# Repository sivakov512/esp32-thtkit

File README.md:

# ESP32 THT Development Kits
**Ultra-Compact Through-Hole Development Boards for ESP32**

This repository contains design files and documentation for ultra-compact, through-hole (THT) friendly development boards based on Espressif ESP32 microcontrollers. These boards are designed for easy integration into breadboard and other through-hole prototyping environments.

## Available Development Kits

| DevKit | Description | SoC | Features |
|--------|-------------|-----|----------|
| [ESP32-C3-THTKIT](esp32-c3-thtkit/) | Ultra-compact ESP32-C3 development board with THT headers | ESP32-C3FH4 | WiFi, Bluetooth 5 (LE), RISC-V single-core |
| [ESP32-H2-THTKIT](esp32-h2-thtkit/) | Ultra-compact ESP32-H2 development board with THT headers | ESP32-H2FH4 | 802.15.4 (Thread, Zigbee), Bluetooth 5 (LE), RISC-V single-core |

## Key Features

- **Ultra-compact form factor**: Minimal dimensions for tight integration
- **Breadboard friendly**: Design optimized for breadboard prototyping
- **THT headers**: Standard 2.54mm pitch through-hole pins
- **Smart header layout**: Bottom header deliberately offset by 1.27mm (half pitch) to prevent accidental shorts in breadboards
- **Simple power supply**: 3.3V to 12V input with onboard LDO
- **Essential pins exposed**: Focused on providing the most important functionality
- **UART debug access**: Dedicated UART pins for easy programming and debugging
- **KiCad design files**: Complete open-source hardware design

## Design Philosophy

These development kits are designed with several principles in mind:
- **Minimal but complete**: Only essential components while maintaining full functionality
- **Direct integration**: Design that works in final projects, not just for prototyping
- **Hackable**: Easy to modify and adapt to specific needs
- **Open design**: Full schematics and PCB files available

## Getting Started

Visit each development kit's directory for specific documentation:

- [ESP32-C3-THTKIT Documentation](esp32-c3-thtkit/)
- [ESP32-H2-THTKIT Documentation](esp32-h2-thtkit/)

## License

This project is released under the [MIT License](LICENSE).

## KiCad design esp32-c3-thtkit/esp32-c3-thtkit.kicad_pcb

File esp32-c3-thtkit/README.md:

# ESP32-C3-THTKIT
**Ultra-Compact THT-Friendly DevKit**

---

## Overview

ESP32-C3-THTKIT is an ultra-compact development board based on the ESP32-C3FH4 SoC. Designed for direct THT integration, it exposes only essential functionality in a minimal form factor. UART pins are easily accessible at the top for in-circuit development.

---

## Pinout

- Left header (THT): VIN, GPIO2 to GPIO19
- Right header (THT): GND, GPIO17 to GPIO12 (FSPI2 by default)
- Bottom header (THT): GPIO4 to GPIO7 (JTAG by default)
- Top edge: UART TX/RX pins
- BOOT/RESET: pad-based activation (short to GND)
- Pin pitch: 2.54 mm standard
- Bottom header deliberately offset by 1.27 mm (half pitch) to prevent accidental shorts when inserted into a breadboard

---

## Programming & Debugging

- UART programming recommended via top pins
- JTAG available on bottom header (default mapping)
- No USB functionality

---

## Electrical

- Input Voltage: 3.3V to 12V
- On-board LDO stabilizes to 3.3V
- No onboard USB

---

## Mechanical

- Dimensions: 24.47 mm x 17.88 mm
- 3x THT headers: left, right, and optional bottom (user-soldered)

---

## Datasheet

[📄 ESP32-H2-THTKIT Datasheet (PDF)](docs/Datasheet.pdf)

[📄 ESP32-H2 Datasheet (Espressif)](https://cdn.jsdelivr.net/gh/sivakov512/kicad-library@master/datasheets/MCU/Espressif/Espressif_ESP32-H2.pdf)

---

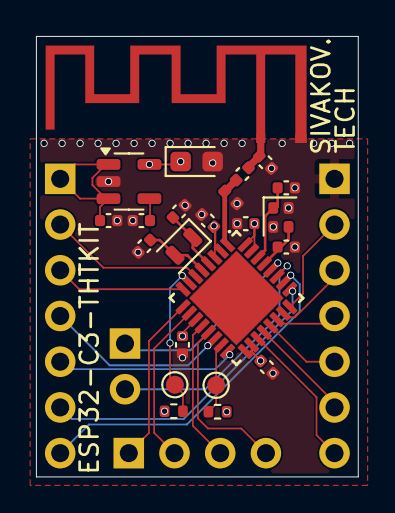
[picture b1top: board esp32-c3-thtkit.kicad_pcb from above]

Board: 4 copper layers, 17.9 x 24.5 mm, 27 parts (0 on the bottom side), 30 nets.

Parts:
AE1: Antenna_Chip; Antenna_PCB_Espressif_2.4GHz_Left
C1: 1m 6.3V X7R; C_0402_1005Metric
C2: 470p 6.3V X7R; C_0402_1005Metric
C3: 2.2m 6.3V TANT; CP_EIA-2012-12_Kemet-R
C4, C5, C6, C8: 100n 6.3V X7R; C_0402_1005Metric
C7: 5.6p C0G; C_0402_1005Metric
C9: 2.2p C0G; C_0402_1005Metric
C10, C13: 15p 6.3V C0G; C_0402_1005Metric
C11, C12: 25p 6.3V C0G; C_0402_1005Metric
J1: PIN_GROUP_1; PinHeader_1x07_P2.54mm_Vertical_NoSilk
J2: PIN_GROUP_3; PinHeader_1x07_P2.54mm_Vertical_NoSilk
J3: PIN_GROUP_2; PinHeader_1x04_P2.54mm_Vertical_NoSilk
J4: UART; PinHeader_1x02_P2.54mm_Vertical_NoSilk
L1: 3.9 nH; L_0402_1005Metric
R1, R2: 10k; R_0402_1005Metric
TP1, TP2: TestPoint; TestPoint_Pad_D1.0mm
U1: MIC5219-3.3YM5; SOT-23-5
U2: ESP32-C3; VFQFN_32_1EP_5x5mm_P0.5mm_EP3.2x3.2mm_Compact
Y1: 32.768kHz ±20ppm CL12.5pF; Crystal_SMD_2012-2Pin_2.0x1.2mm
Y2: 40MHz ±10ppm CL8pF; Crystal_SMD_1612-4Pin_1.6x1.2mm

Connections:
+3.3V: C3.1, C4.2, C5.2, C6.2, C8.2, R1.2, R2.2, U1.5 (OUT), U2.2 (VDD3P3), U2.3 (VDD3P3), U2.11 (VDD3P3_RTC), U2.17 (VDD3P3_CPU), U2.18 (VDD_SPI), U2.31 (VDDA), U2.32 (VDDA)
/BOOT: R1.1, TP1.1, U2.15 (GPIO9)
/GPIO2: J2.2, U2.6 (GPIO2)
/GPIO3: J2.3, U2.8 (GPIO3)
/GPIO8: J2.4, U2.14 (GPIO8)
/GPIO10: J2.5, U2.16 (GPIO10)
/GPIO18: J2.6, U2.25 (GPIO18)
/GPIO19: J2.7, U2.26 (GPIO19)
/MTCK: J3.3, U2.12 (MTCK)
/MTDI: J3.2, U2.10 (MTDI)
/MTDO: J3.4, U2.13 (MTDO)
/MTMS: J3.1, U2.9 (MTMS)
/RESET: R2.1, TP2.1, U2.7 (CHIP_EN)
/RF: C7.2, L1.1, U2.1 (LNA_IN)
/SPICLK: J1.4, U2.22 (SPICLK)
/SPICS0: J1.5, U2.21 (SPICS0)
/SPID: J1.3, U2.23 (SPID)
/SPIHD: J1.7, U2.19 (SPIHD)
/SPIQ: J1.2, U2.24 (SPIQ)
/SPIWP: J1.6, U2.20 (SPIWP)
/U0RXD: J4.2, U2.27 (U0RXD)
/U0TXD: J4.1, U2.28 (U0TXD)
/XTAL_32K_N: C12.2, U2.5 (XTAL_32K_N), Y1.2
/XTAL_32K_P: C11.2, U2.4 (XTAL_32K_P), Y1.1
/XTAL_N: C13.2, U2.29 (XTAL_N), Y2.3
/XTAL_P: C10.1, U2.30 (XTAL_P), Y2.1
GND: AE1.2 (PCB_Trace), C1.1, C2.1, C3.2, C4.1, C5.1, C6.1, C8.1, C9.1, C10.2, C11.1, C12.1, C13.1, J1.1, L1.2, U1.2 (GND), U2.33 (GND), Y2.2, Y2.4
unnamed: AE1.1 (FEED), C7.1, C9.2
unnamed: C2.2, U1.4 (BP)
VIN: C1.2, J2.1, U1.1 (IN), U1.3 (EN)

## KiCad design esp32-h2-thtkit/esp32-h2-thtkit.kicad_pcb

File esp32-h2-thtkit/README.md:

# ESP32-H2-THTKIT
**Ultra-Compact THT-Friendly DevKit**

---

## Overview

ESP32-H2-THTKIT is an ultra-compact development board based on the ESP32-H2FH4 SoC. Designed for direct integration into through-hole (THT) projects, it contains only the essential components and remains breadboard-friendly. UART debug pins are routed to the top for easy access during development, regardless of installation density.

---

## Pinout

- Left header (THT): GPIO0 to GPIO5 (also FSPI2-capable)
- Right header (THT): VIN, GND, GPIO27 to GPIO22
- Bottom header (THT): GPIO8, GPIO10, GPIO11, GPIO12 (can be used as JTAG)
- Top edge: UART TX/RX pins
- BOOT/RESET: pad-based activation (short to GND)
- Pin pitch: 2.54 mm standard
- Bottom header deliberately offset by 1.27 mm (half pitch) to prevent accidental shorts when inserted into a breadboard

---

## Programming & Debugging

- UART programming recommended via top pins
- JTAG support via GPIO8/10/11/12 (if remapped)
- No USB functionality

---

## Electrical

- Input Voltage: 3.3V to 12V
- On-board LDO stabilizes to 3.3V
- No onboard USB

---

## Mechanical

- Dimensions: 21.8 mm x 17.88 mm
- 3x THT headers: left, right, and optional bottom (user-soldered)

---

## Datasheet

[📄 ESP32-C3-THTKIT Datasheet (PDF)](docs/Datasheet.pdf)

[📄 ESP32-C3 Datasheet (Espressif)](https://cdn.jsdelivr.net/gh/sivakov512/kicad-library@master/datasheets/MCU/Espressif/Espressif_ESP32-C3.pdf)

---

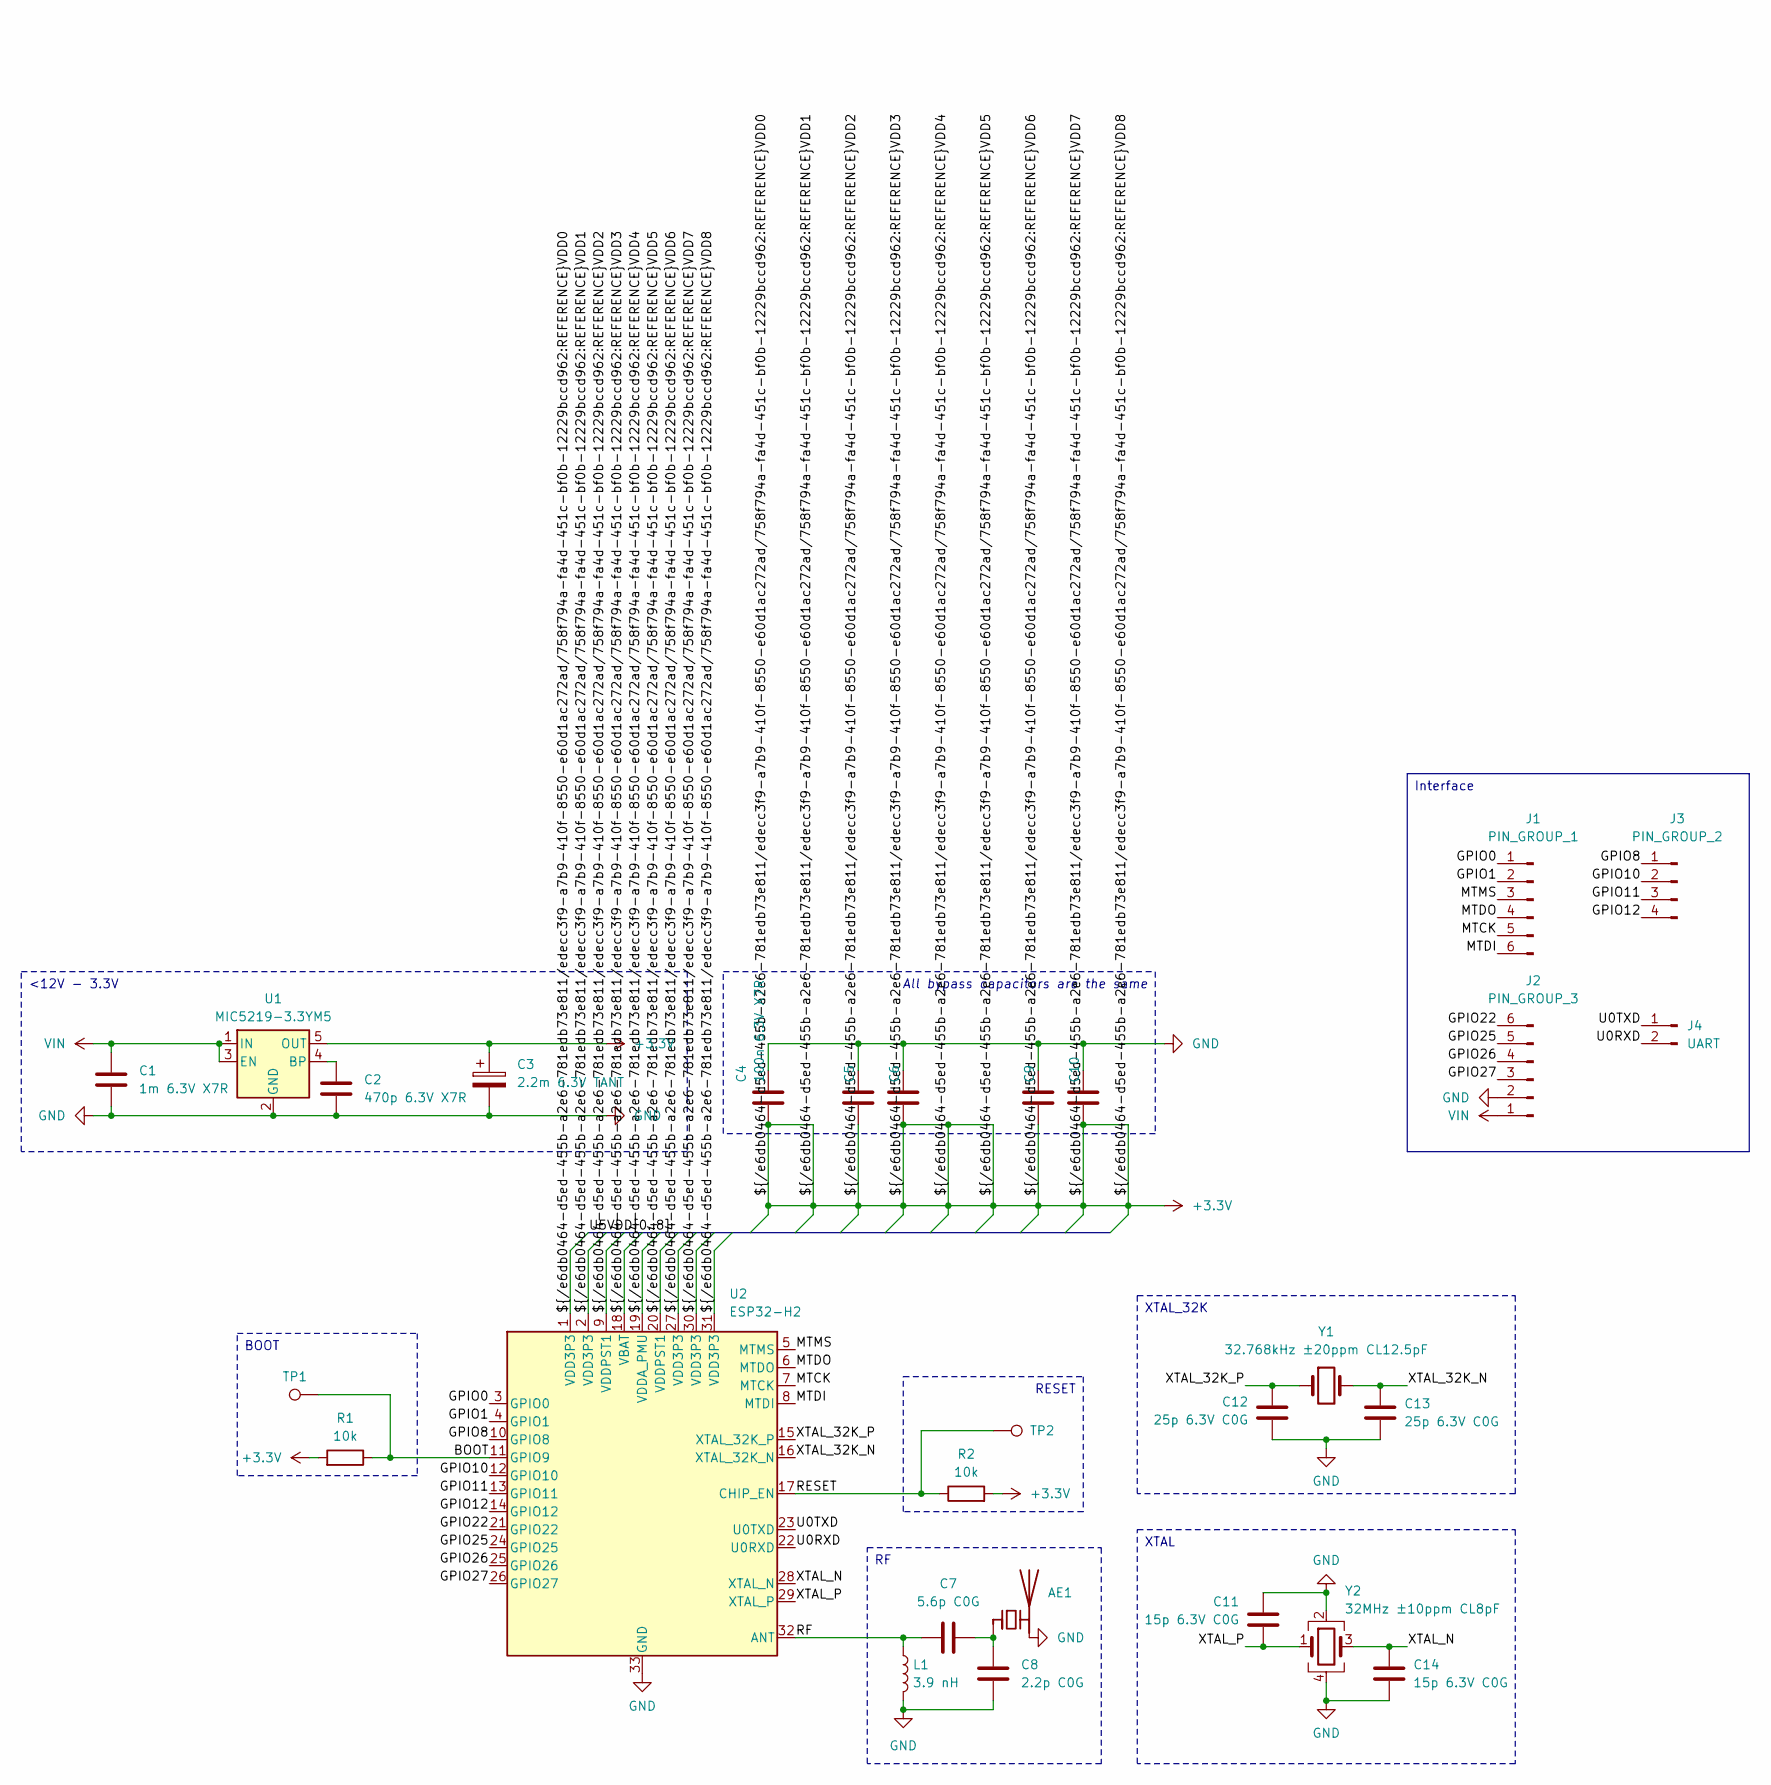
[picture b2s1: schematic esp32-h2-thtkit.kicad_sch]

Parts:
AE1: Antenna_Chip; Antenna_PCB_Espressif_2.4GHz_Right
C1: 1m 6.3V X7R; C_0402_1005Metric; LCSC PN C307427
C2: 470p 6.3V X7R; C_0402_1005Metric; LCSC PN C1537
C3: 2.2m 6.3V TANT; CP_EIA-2012-12_Kemet-R; LCSC PN C444770
C4, C5, C6, C9, C10: 100n 6.3V X7R; C_0402_1005Metric; LCSC PN C309458
C7: 5.6p C0G; C_0402_1005Metric; LCSC PN C1574
C8: 2.2p C0G; C_0402_1005Metric; LCSC PN C1559
C11, C14: 15p 6.3V C0G; C_0402_1005Metric; LCSC PN C1548
C12, C13: 25p 6.3V C0G; C_0402_1005Metric; LCSC PN C1556
J1: PIN_GROUP_1; PinHeader_1x06_P2.54mm_Vertical_NoSilk
J2: PIN_GROUP_3; PinHeader_1x06_P2.54mm_Vertical_NoSilk
J3: PIN_GROUP_2; PinHeader_1x04_P2.54mm_Vertical_NoSilk
J4: UART; PinHeader_1x02_P2.54mm_Vertical_NoSilk; LCSC PN C7501580
L1: 3.9 nH; L_0402_1005Metric; LCSC PN C77109
R1, R2: 10k; R_0402_1005Metric; LCSC PN C25744
TP1, TP2: TestPoint; TestPoint_Pad_D1.0mm
U1: MIC5219-3.3YM5; SOT-23-5; LCSC PN C29613
U2: ESP32-H2; TQFN_32_1EP_4x4mm_P0.4mm_EP2.4x2.4mm_Compact; LCSC PN C22470214
Y1: 32.768kHz ±20ppm CL12.5pF; Crystal_SMD_2012-2Pin_2.0x1.2mm; LCSC PN C55208
Y2: 32MHz ±10ppm CL8pF; Crystal_SMD_1612-4Pin_1.6x1.2mm; LCSC PN C7301921

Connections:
+3.3V: C3.1, C4.2, C5.2, C6.2, C9.2, C10.2, R1.2, R2.2, U1.5 (OUT), U2.1 (VDD3P3), U2.2 (VDD3P3), U2.9 (VDDPST1), U2.18 (VBAT), U2.19 (VDDA_PMU), U2.20 (VDDPST1), U2.27 (VDD3P3), U2.30 (VDD3P3), U2.31 (VDD3P3)
/BOOT: R1.1, TP1.1, U2.11 (GPIO9)
/GPIO0: J1.1, U2.3 (GPIO0)
/GPIO1: J1.2, U2.4 (GPIO1)
/GPIO8: J3.1, U2.10 (GPIO8)
/GPIO10: J3.2, U2.12 (GPIO10)
/GPIO11: J3.3, U2.13 (GPIO11)
/GPIO12: J3.4, U2.14 (GPIO12)
/GPIO22: J2.6, U2.21 (GPIO22)
/GPIO25: J2.5, U2.24 (GPIO25)
/GPIO26: J2.4, U2.25 (GPIO26)
/GPIO27: J2.3, U2.26 (GPIO27)
/MTCK: J1.5, U2.7 (MTCK)
/MTDI: J1.6, U2.8 (MTDI)
/MTDO: J1.4, U2.6 (MTDO)
/MTMS: J1.3, U2.5 (MTMS)
/RESET: R2.1, TP2.1, U2.17 (CHIP_EN)
/RF: C7.2, L1.1, U2.32 (ANT)
/U0RXD: J4.2, U2.22 (U0RXD)
/U0TXD: J4.1, U2.23 (U0TXD)
/XTAL_32K_N: C13.2, U2.16 (XTAL_32K_N), Y1.2
/XTAL_32K_P: C12.2, U2.15 (XTAL_32K_P), Y1.1
/XTAL_N: C14.2, U2.28 (XTAL_N), Y2.3
/XTAL_P: C11.1, U2.29 (XTAL_P), Y2.1
GND: AE1.2 (PCB_Trace), C1.1, C2.1, C3.2, C4.1, C5.1, C6.1, C8.1, C9.1, C10.1, C11.2, C12.1, C13.1, C14.1, J2.2, L1.2, U1.2 (GND), U2.33 (GND), Y2.2, Y2.4
unnamed: AE1.1 (FEED), C7.1, C8.2
unnamed: C2.2, U1.4 (BP)
VIN: C1.2, J2.1, U1.1 (IN), U1.3 (EN)

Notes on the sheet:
XTAL
RESET
XTAL_32K
All bypass capacitors are the same
BOOT
Interface
<12V - 3.3V

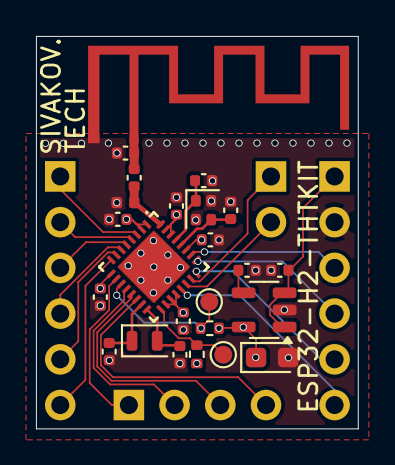
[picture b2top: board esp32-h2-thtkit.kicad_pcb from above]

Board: 4 copper layers, 17.9 x 21.8 mm, 28 parts (0 on the bottom side), 28 nets.

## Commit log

2025-05-28 Ignore KiCad specific stuff
2025-05-28 Define esp32-h2 schematic
2025-05-28 Use connectors without silkscreen to place them right on the corner
2025-05-28 Basic components layout
2025-05-29 Full schematic and PCB layout for esp32-h2 tht kit
2025-05-29 Added 32k crystal, updated footprint, few rearranges
2025-06-01 Improve layout to make better SPI routes
2025-06-02 Fix antenna layout a bit
2025-06-02 The same devkit for C3
2025-06-02 Change some manufacturing related attributes
2025-06-02 Draw pin layout on user layer
2025-06-02 esp32-c3-thtkit documentation
2025-06-02 esp32-h2-thtkit documenation
2025-06-03 Clarify bottom header offset purpose in documentation
2025-06-03 Add ESP32 THT development kits documentation
2025-06-04 Make devkits cheaper by using 0402 components instead of 0201
2025-06-05 Change microcontroller package from 4x4 to 5x5
2025-06-09 Unify schemas and fix esp32-c3 footprint
